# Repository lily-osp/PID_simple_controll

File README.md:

# BLDC Motor PID Controller (ESP32-C3)

Fixed-target PID controller for BLDC motors on the ESP32-C3, run bare-metal
for compute (no WiFi, no BLE). Holds 1440 RPM via a 200Hz FreeRTOS loop.

> History: this project previously shipped Arduino Uno and ATtiny85 variants.
> They were removed on 2026-10-31 (commit `396ade7`) and remain in git history.

## Overview

Single-platform implementation targeting the ESP32-C3 SuperMini. The C3 is
used for its 160MHz RISC-V core and hardware FPU; no wireless stack is used.
Two firmware builds share one set of drivers: a bench build for bring-up and
a production build for the enclosure.

| Build | Status | Use Case | Key Features |
|-------|--------|----------|--------------|
| **`esp32-c3/control/`** | Bench | Bring-up, service, Hall-line trials | Serial console, telemetry, trial scoring |
| **`esp32-c3/embedded/`** | Production | Enclosure deployment | Silent, autonomous, arming + stall failsafe |

## Key Features

- **200Hz Control Loop**: High-frequency PID updates via dedicated FreeRTOS task
- **Hardware-Accelerated PWM**: ESP32 LEDC peripheral generating smooth 5kHz motor control signals
- **Interrupt-Driven RPM**: High-precision pulse counting using IRAM-resident ISR
- **Sliding Window Filter**: 12-sample window + IIR smoothing for stable control input
- **ESC Arming + Soft-Start**: 2s zero-throttle arm, then 1.5s power ramp
- **FPU Utilization**: Full floating-point PID calculations for maximum precision
- **Safety Features**: Stall failsafe, emergency stop, input validation

## Quick Start

### 1. Hardware Requirements

- ESP32-C3 SuperMini (or compatible) + USB-C cable
- 3-Phase BLDC Motor with Hall Effect sensors
- PWM-compatible ESC / motor driver (e.g., JYQD V7.3E)
- Power supply appropriate for motor voltage requirements
- Voltage divider (2.2kΩ/3.3kΩ) if using 5V Hall sensors

### 2. Installation Steps

```bash
git clone https://github.com/your-repo/PID_simple_controll.git
cd PID_simple_controll
```

**Configure for your motor**:
1. Edit `esp32-c3/control/config.h` (pins, motor, PPR)
2. Edit `esp32-c3/control/config_common.h` (PID gains)
3. Configure pin assignments if using custom wiring

**Upload firmware**:
- Use Arduino IDE with ESP32 board support, or `arduino-cli`:

```bash
arduino-cli compile -b esp32:esp32:nologo_esp32c3_super_mini esp32-c3/embedded
arduino-cli upload  -p /dev/ttyACM0 -b esp32:esp32:nologo_esp32c3_super_mini esp32-c3/embedded
```

Which build to flash: see [esp32-c3/BUILDS.md](esp32-c3/BUILDS.md).

## Platform Details

### ESP32-C3 (`esp32-c3/`)

**Processor**: RISC-V @ 160MHz with hardware FPU

**Firmware Builds**:

**Bench (`control/`)**: Serial console for bring-up and service.
- Command parser, telemetry, diagnostics console
- Trial log auto-scores each power cycle to rank Hall permutations
- Full visibility into PID state and RPM estimation

**Production (`embedded/`)**: Silent, autonomous build for the enclosure.
- Control loop, ESC arming, soft-start, stall failsafe
- Shares the exact RPM estimator, PID, and LEDC drivers with the bench build

**Features**:
- Hardware FPU for fast floating-point calculations
- FreeRTOS ensures deterministic timing
- 3.3V logic level (requires voltage divider for 5V sensors)
- Comprehensive debugging via Serial Monitor (bench build)

Full architecture: [esp32-c3/README.md](esp32-c3/README.md).

### Custom Driver PCB (`PCB/V1/`)

Full-integration **64 × 98 mm, 4-layer** board combining the firmware above with its own
driver hardware — no external ESC needed:

- **JYQD-V7.3E3 architecture**: JY01 controller + JY213L gate driver + JY2605M
  half-bridges (same silicon as the reference driver board)
- **ESP32-C3 Super Mini** onboard as the controller (FG/PWM/VR/EL/trim pot)
- **Hall signal conditioner**: RC filter → LM324 (×11) → 74HC14 Schmitt trigger
- **Power tree**: V_IN → 7812 → +12V → 7805 → +5V

Design files, port pinouts, and build scripts: [PCB/V1/README.md](PCB/V1/README.md).
Bring-up procedure: [PCB/V1/TESTPLAN.md](PCB/V1/TESTPLAN.md).

## Documentation

### Comprehensive Guides

- **[Hardware Assembly Guide](docs/howto.md)**: Wiring guide, pin assignments, and connection diagrams
- **[Bench Wiring — stock JYQD + ESP32](docs/bench_wiring.md)**: Run the firmware on a stock JYQD-V7.3E3 and a bare Super Mini, before the custom PCB
- **[Troubleshooting Guide](docs/mitigation.md)**: Comprehensive diagnosis and solutions for common issues
- **[ESP32-C3 README](esp32-c3/README.md)**: Architecture, firmware, and hardware setup
- **[Builds](esp32-c3/BUILDS.md)**: Production vs bench firmware, and how they share code
- **[Diagnostics Guide](esp32-c3/DIAGNOSTICS.md)**: Serial console commands and fault isolation
- **[Driver PCB](PCB/V1/README.md)**: 64 × 98 mm 4-layer ESP32-C3 + JYQD-architecture driver board
- **[PCB Test Plan](PCB/V1/TESTPLAN.md)**: Staged bring-up procedure and failure diagnosis

## Configuration

### Motor Configuration

Settings live in `esp32-c3/*/config.h`:

```cpp
#define PULSES_PER_REV  4     // Set based on motor pole count
#define DEFAULT_TARGET_RPM 1440.0  // Target speed in RPM
```

**Calculating PULSES_PER_REV**: For a motor with N poles using single Hall sensor: `PULSES_PER_REV = N / 2`

Example: 8-pole motor = 4 pulses per revolution

### PID Tuning

PID constants are defined in `esp32-c3/control/config_common.h`:

```cpp
#define DEFAULT_KP  0.150  // Proportional gain
#define DEFAULT_KI  0.080  // Integral gain
#define DEFAULT_KD  0.015  // Derivative gain
```

**Tuning Process**:
1. Begin with Kp only (set Ki and Kd to 0)
2. Increase Kp until oscillation occurs, then reduce by 30%
3. Add Ki gradually to eliminate steady-state error
4. Add small Kd if overshoot occurs
5. Watch the bench console telemetry to verify stability

## Safety Considerations

1. **Electrical Isolation**: Keep logic power separate from motor power (common ground only)
2. **Voltage Protection**: Use voltage dividers when interfacing 5V sensors with 3.3V logic
3. **Mechanical Safety**: Secure motor firmly and remove propellers during initial testing
4. **Emergency Stop**: Keep power disconnect easily accessible during testing
5. **Current Rating**: Ensure power supply can handle motor startup current (typically 2-3x running current)
6. **Thermal Management**: Monitor ESC and motor temperatures during extended operation

## Troubleshooting Quick Reference

| Issue | Likely Cause | Solution |
|-------|--------------|----------|
| Motor doesn't start | Insufficient PWM threshold | Increase `PWM_MIN_THRESHOLD` to 60-80 |
| RPM reading 2x actual | Wrong `PULSES_PER_REV` | Divide current value by 2 |
| Unstable speed | Poor PID tuning or noise | Reduce Kp by 30%, add filtering |
| Random RPM spikes | Electrical noise | Add 0.1µF capacitor to Hall input |
| ESP32-C3 damaged | 5V applied to GPIO | Use voltage divider for all 5V signals |

See [Troubleshooting Guide](docs/mitigation.md) for comprehensive solutions.

## Contributing

Contributions are welcome. Areas of interest:
- Advanced PID algorithms (adaptive, fuzzy logic)
- Enhanced filtering techniques
- PCB designs for production deployment
- Test cases and validation procedures

Please read [CONTRIBUTING.md](CONTRIBUTING.md) for guidelines.

## License

MIT License - See [LICENSE](LICENSE) file for details.

This project is provided as-is for educational and commercial use. No warranty is provided for fitness for any particular purpose.

## Support

- **Issues**: Report bugs and request features via GitHub Issues
- **Discussions**: Ask questions and share experiences in GitHub Discussions
- **Documentation**: Comprehensive guides available in `docs/` directory

## Acknowledgments

Built with focus on reliability, performance, and practical deployment. Tested in real-world applications across multiple motor types and configurations.

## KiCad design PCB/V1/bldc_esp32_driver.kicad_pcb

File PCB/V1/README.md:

# BLDC Motor Driver — JYQD-V7.3E3 Architecture + ESP32-C3 Super Mini + Hall Amp

Custom **64 × 98 mm, 4-layer** PCB (full-integration) based on the **JYQD-V7.3E3** brushless driver
architecture, with an **ESP32-C3 Super Mini** controller and a Hall sensor signal
conditioner (RC filter → LM324 gain ×11 → 74HC14 Schmitt trigger).

> `JYQD-V7.3E3-English.pdf` is a product datasheet (specs + wiring), not a schematic.
> The circuit follows the JY family — **JY01** (SOP-16 controller) and **JY2605M**
> (PowerPAK SO-8 dual N-MOS, 60 V / 50 A / 14 mΩ) — the same silicon as the reference
> board. The gate driver is a **Fortior FD6288T** (TSSOP-20), which is pin-for-pin
> identical to the JY213L of the reference board but is stocked by LCSC (C97683).
> Datasheets for all three are in `docs/controller_specification/`.

## External interface (fully integrated — 3 connectors only)

Everything else is handled on-board by the ESP32 (speed/direction/enable are driven
internally to the JY01). No control port, no GPIO breakouts.

| Connector | Pins | Function | Pitch |
|---|---|---|---|
| **J5** power | `P+  P−` | +12 V (V_IN) and ground | 5.00 mm (MaiXu MX126) |
| **J6** motor | `MA  MB  MC` | phase A / B / C to BLDC | 5.00 mm (MaiXu MX126) |
| **J3** Hall | `GND  Hc  Hb  Ha  5V` | Hall sensors (powered from 5 V) | 2.54 mm |

## Architecture

```
 V_IN ── 7812 ── +12V ── 7805 ── +5V
   │                │          │
 JY01 ──gate R── FD6288T ─gate R── JY2605M ×3 ── phases A/B/C (J6)
   │                │
 Hall amp (5V): RC → LM324(×11) → 74HC14 → JY01 Hall inputs
 ESP32-C3: FG (scaled) / PWM → VR / EL / trim pot
```

- **Power tree**: `V_IN` (J5 P+) → U8 L7812 → `+12V` (gate-driver VCC) → U7 L7805 →
  `+5V` (logic). Hall amp runs on **+5V**, so 74HC14 outputs drive JY01 directly.
- **Current sense**: the bridge return (`GND`) passes through the R1 shunt (5 mΩ, 2512)
  to `PNEG` = J5 P−. **U1's `Vss` is tied to `PNEG`, not to the ground pour**, so the
  `Is` pin (fed from the `GND` side of the shunt through R36 + C21) sees a *positive*
  I·R. Referencing `Vss` to the pour instead — as V1 did — makes `Is` read negative and
  the JY01's constant-current and overload trips never fire. The offset this puts on
  U1's other pins is ≤ I·R ≈ 75 mV at 15 A, far inside its logic margins.
  Trip points, per the JY01 datasheet: constant-current at `Is` = 0.1 V (20 A across
  5 mΩ), shutdown at 0.2 V. Lower R1 to size them for a smaller motor.

## Design notes

- **78xx regulators**: with 12–36 V input keep `V_IN ≤ 28 V` for dropout/power margin
  (12 V nominal recommended).
- **PWM → VR**: GPIO1 drives the JY01 `VR` node through **R7 (100 Ω)**, directly. The
  JYQD datasheet accepts PWM 1–20 kHz on `VR` and averages it internally, so no level
  shifter is needed. Max drive is 3.3 V of the 0.1–5 V range ≈ 66 % speed.
- **GPIO4 → EL level shift**: EL is pulled up to **+5V** (R33 10 kΩ); GPIO4 drives it
  open-drain through R34 (1 kΩ). Configure GPIO4 as open-drain in firmware. Per the
  JYQD datasheet, EL high/floating **allows** operation and GND forbids it, so the
  motor is enabled by default at power-up.
- **FG scaling**: JY01 FG (5 V) → R4 2.2 k / R5 3.3 k divider → GPIO0 (RPM in, 3.3 V).
- **ESP32 pin usage**: GPIO0=RPM (FG), GPIO1=PWM→VR, GPIO2=**unconnected** (boot
  strapping pin, internal pull-up holds it high), GPIO3=trim ADC (ADC1_CH3),
  GPIO4=EL (open-drain), GPIO5=ERR LED. GPIO6–10/20/21 are spare/unconnected.
- **ERR LED** driven from GPIO5 via R32 (560 Ω); **PWR LED** from +5V via R20 (560 Ω).

## 2026-11 rework — sourcing fix + three real bugs

Driven by `tools/v2_power_stage_rework.py` (board) and `tools/gen_sch_full.py`
(schematic); both are re-runnable and idempotent. After it: **DRC 0 errors / 0
warnings / 0 unconnected**, and every pad's net matches the schematic netlist.

| # | What was wrong | What changed |
|---|---|---|
| 1 | `U3` (JY213L) is not in the LCSC catalogue | **U3 is now a Fortior FD6288T (C97683)** — same TSSOP-20 land, same pin order (1-3 HIN, 4-6 LIN, 7 VCC, 8 COM, 9-11 LO3..LO1, 12-14 VS3/HO3/VB3, 15-17 phase 2, 18-20 phase 1). 250 V instead of 90 V, 1.5/1.8 A outputs, 200 ns dead time. It has **no internal bootstrap diodes** (the JY213L does), which is why D1–D3 stay. No copper moved. |
| 2 | `Q2–Q4` used an invented DFN-8 footprint: eight 1.6 × 0.65 mm pads on opposite edges, no thermal pads — it does not match the real JY2605M and could not carry the current | **New land `footprints/JY2605M_PowerPAK_SO8_Dual.kicad_mod`**, derived from KiCad's vetted `PowerPAK_SO-8_Dual` and renumbered to the datasheet pinout **1 = S1, 2 = G1, 3 = S2, 4 = G2, 5,6 = D2, 7,8 = D1**. The symbol was rewritten to match (the old one invented `G_H/D_H/S_H/…`). |
| 3 | `U1` pins 9–12 were wired 9 = BB, 10 = BT, 11 = CB, 12 = CT | The JY01 datasheet says **9 = BT, 10 = BB, 11 = CT, 12 = CB**. On the B and C legs the chip's top-arm output drove the bottom FET and vice versa, so the motor could not commutate (no shoot-through — the JY01 never asserts both arms of one leg — but it would cog or stall). Fixed. |
| 4 | `Is` could never trip | U1's `Vss` sat on the ground pour, i.e. the **high** side of the R1 shunt, so `Is` saw a negative voltage and the constant-current and overload protections were dead. `Vss` and the C21 filter return now sit on `PNEG` (connector side); R36's cold end moved to the pour. See *Current sense* above. |

**How the half-bridge is formed.** The JY2605M is two independent FETs, not an
internally-connected half-bridge, so the board makes the bridge: D1 (left pad) = `V_IN`,
S1 (bottom-left lead) = phase, D2 (right pad) = phase, S2 = `GND`, G1/G2 = gates. Each
part is rotated 90°, drains up, leads down. The phase node therefore has to get from the
bottom-left lead to the right-hand pad: it drops to a via pair under the package, crosses
on **In1.Cu** as a 2 mm wrap, and comes back up east of the part. In1.Cu carried no
routing before, so the three wraps are the only cuts in that plane.

**Gate fan-out.** The six gate stubs drop into a via row 1.6 mm below each package and run
west-to-east on **B.Cu** in six lanes (79.6 → 82.6 mm, 0.6 mm apart), each lane joining the
existing In2.Cu run from its 15 Ω resistor at a hand-off via (x = 132.3 → 136.4 mm). Lane
depth increases as the target moves west, so no lane crosses another.

**Where the JY01 pin-order fix was made.** The chain `U1 pin → 100 Ω → FD6288T input` is
correct end to end, so the crossing is undone once, at the driver's inputs, where there is
room: the four approaches to U3 pins 2/3/5/6 are re-routed (two hops on In1.Cu, one on
B.Cu, one extended on In2.Cu). The two 100 Ω pairs are identical parts, so `R10`/`R11` and
`R12`/`R13` swap reference designators to follow the function they now serve.

**3D model.** The new footprint ships a hand-built VRML body
(`Custom.3dshapes/JY2605M_PowerPAK_SO8_Dual.wrl`) so Q2–Q4 appear as real packages in
`render/routed_top.png` instead of bare pads — the old DFN footprint had no model at all.
Representative geometry for visualisation, not mechanical clearance work.

**Test points.** TP19/TP21/TP22/TP27 (the four western gate probes) moved onto the new gate
vias and shrank to 1.0 mm; their silkscreen numbers moved with them. TP20 and TP23 are
unchanged. New coordinates are in [`TESTPLAN.md`](TESTPLAN.md).

**Still hand-fitted:** U1 (JY01) and Q2–Q4 (JY2605M) — both Shanghai Juyi parts, sold on
that company's Taobao store (shop `301588897`) and through juyitech.com; datasheets are in
`docs/controller_specification/`. If a fully LCSC-sourced power stage is ever wanted, the
drop-ins are six singles — TM80N06NF (C7422888, DFN5x6, 60 V / 80 A / 5.2 mΩ) or
NCE6050KA (C96013, TO-252) — which needs a new power-stage layout, not just a footprint.

## Pre-order audit

Checks performed on the exact fabrication data (`fab/`), all passing:

| Check | Result |
|---|---|
| DRC (`--severity-all`) | 0 violations, 0 unconnected items |
| Schematic parity | 0 genuine (266 cosmetic: root-sheet `/` prefix, footprint lib prefix) |
| Outline closure | closed Edge.Cuts loop, 0 open endpoints, 64.1 × 98.1 mm |
| Pads outside outline | 0 |
| Orphan nets (1 pad) | none |
| Fab files | 11 gerbers (4 copper) + 1 drill (Excellon, metric, decimal) + job file |
| Solder mask | 238 front / 33 rear openings (205 SMD + 29 THT + 4 NPTH); 0.05 mm expansion, 0.10 mm min web |
| Paste | 205 front apertures (1:1 with the SMD pads), none on the rear |

### Electrical fixes applied at audit

- **Bootstrap caps C13–C15 were 10 µF/25 V.** The `VB_x` rail floats on the phase and
  peaks at `V_IN + (V_+12V − V_f)` ≈ **V_IN + 11.3 V**. At the intended 12 V input that
  is 23.3 V (93 % of the rating); at 24 V input it is 35.3 V and the part fails short,
  taking the JY213L with it. Changed to **1 µF/50 V**, which is also the correct
  bootstrap value for this gate charge (droop ≈ Q_g/C ≈ 50 mV/cycle). Footprint
  unchanged (0805).
- **Unrated 0805 caps on rails** were given explicit ratings: `C12 → 10 µF/25 V` (it sits
  on +12 V), `C11/C19/C20 → 100 nF/50 V`.

### Layout changes applied at audit

1. **Trim pot moved off the strapping pin.** `RV1`'s wiper was on `GPIO2`, one of the
   three ESP32-C3 strapping pins (GPIO2/8/9), which must be high or floating at boot. The
   pot pulls it to 0 V at the low end of travel, so a power cycle with the pot turned
   down could enter joint-download boot instead of running firmware. The net now goes to
   `GPIO3` (`ADC1_CH3`, not a strapping pin); only the final 1.31 mm stub was rerouted,
   the 20 mm trunk is untouched. `GPIO2` is left floating, which is exactly the state its
   internal boot pull-up wants.
2. **Firmware followed the pin move.** `POT_SENSITIVITY_PIN` is now 3 and the
   `POT_ENABLE_PIN` gate is gone — the trim is always active and the pot midpoint is
   1.0×. Previously the firmware expected the enable on `GPIO3` while the board left it
   unconnected, so the pot did nothing at all. Both sketches compile (`pio run`,
   espressif32 7.0.1): control 17.9 % flash / 4.3 % RAM, embedded likewise.
3. **Four M3 mounting holes added** at the corner-arc centres (5 mm from each edge),
   NPTH 3.2 mm, marked board-only so they do not appear as schematic-parity extras, with
   a 1.2 mm copper-free ring so a screw head cannot short the GND pour.
4. **`C4` shifted 2.4 mm left** because its 10 mm can sat 0.4 mm from the bottom-right
   hole — an M3 head would have fouled it. Its three track endpoints were snapped to the
   new pad positions; nothing else moved.

### Remaining note

- **`EL` (GPIO4) and the ERR LED (GPIO5) are wired but unused by firmware.** `EL` is
  pulled to +5 V through R33 and driven open-drain through R34, so the JY01 enable state
  at power-up depends on the EL polarity of the JY01 itself — confirm before relying on
  the motor being disabled at boot. Wiring either up is a firmware change only.

## Status

**Folder layout:** `PCB/V1/` is this board. When a smaller revision is attempted it goes
in `PCB/V2/` alongside it, so both stay buildable and comparable.

**The previous board is preserved at git tag `v1`** (commit 837cf5a): 70 × 120 mm,
2 layers. This folder is the current 64 × 98 mm 4-layer board.

| | old (tag `v1`) | this board |
|---|---|---|
| Size | 70 × 120 mm (8400 mm²) | **64 × 98 mm (6272 mm², −25 %)** |
| Layers | 2 | **4** (In1 = solid GND plane) |
| Signal layers | 2 | 3 (F.Cu, In2.Cu, B.Cu) |
| Phase copper (avg) | 0.33–0.39 mm | **0.67–0.74 mm** |
| Traces / vias | 1277 / 142 | 862 / 121 |
| DRC | 0 / 0 | 0 / 0 |

- **Schematic**: complete & verified — netlist matches the design table **223/234 pins**
  (floating pins are the 3 unused 74HC14 gate outputs + 8 spare ESP32 GPIOs).
- **Board**: **fully routed, DRC-clean, fab package generated** — 64.1 mm × 98.1 mm
  (5 mm rounded corners), 97 footprints (67 components + 4 M3 holes + 26 test points).
  - 862 traces, 121 vias, 4 zones (solid GND plane on In1 + GND pours on
    F.Cu / B.Cu / In2.Cu)
  - **DRC: 0 violations, 0 unconnected items** (`kicad-cli pcb drc --severity-all`)
  - **Schematic parity: 0 genuine mismatches** — the 266 reported items are cosmetic only
    (schematic nets carry the root-sheet `/` prefix; footprints are reported without their
    library prefix). Verified programmatically: 0 net-name differences, 0 footprint
    differences after normalisation, 0 extra footprints.
  - **Outline**: closed Edge.Cuts loop, 0 open endpoints; **0 pads outside** the outline.
  - **Drills**: 0.3 mm ×110 and 0.4 mm ×15 (vias), 0.8/1.0/1.1/1.2/1.3 mm ×29
    (component holes), 3.2 mm ×4 (M3 mounting, NPTH).
  - Renders: `render/routed_top.png`, `render/routed_bottom.png`
  - **Bottom silkscreen**: OSP cloud logo (16 mm, vectorised from
    `OSP_1600.png` with potrace into 14 filled polygons) and the credit
    `designed by : github.com/1999azzar`, both on `B.SilkS`.

### Copper sizing (measured, not assumed)

The 4-layer stack gives the phases a dedicated corridor, so they are no longer starved by the 2-layer
clearance wall. Length-weighted averages:

| Net | 2-layer avg | V1 avg | **after the rework** | min | max |
|---|---|---|---|---|---|
| PH_A | 0.33 mm | 0.75 mm | **0.86 mm** | 0.25 mm | 2.00 mm |
| PH_B | 0.35 mm | 0.74 mm | **0.88 mm** | 0.25 mm | 2.00 mm |
| PH_C | 0.39 mm | 0.77 mm | **0.94 mm** | 0.25 mm | 2.00 mm |
| V_IN | 0.80 mm | 0.79 mm | **1.19 mm** | 0.80 mm | 1.50 mm |
| PNEG | 0.80 mm | 0.80 mm | 0.66 mm | 0.40 mm | 0.80 mm |
| +12V / +5V | 0.57 mm | 0.40 mm | 0.40 mm | 0.40 mm | 0.40 mm |

> **Current capability.** Inside the power stage the phase node is a 2.00 mm In1.Cu wrap
> and the V_IN rail is 1.50 mm on 2 oz outer copper; the narrowest part of a phase path is
> the 0.80 mm stub out of the high-side source lead. By IPC-2221 at a 20 °C rise that stub
> sets the limit at **≈ 4.5 A continuous per phase**, with the rest of the path good for
> 8–11 A, and the low-side return leaves through the pour and a via into all four planes.
> That covers the 42BLF motor family's 1.9–5.7 A rated current; it is **not** the 15 A the
> JYQD-V7.3E3 reference board claims, and the board should not be run there.
> `PNEG` now carries only the sense reference and the logic return, so its 0.40 mm
> branches are fine. The `+12V`/`+5V` rails stay at 0.40 mm (~1.5 A on 2 oz) against a
> load of a few hundred mA.

## Component placement (64 × 98 mm)

| Zone | Components |
|---|---|
| Top edge | J5 (power in), J6 (motor out), M3 holes in the corners |
| Bottom edge | J3 (Hall port) |
| Left column | C1/C2/C5 bulk → U8 (7812) → C3 → U7 (7805) → C4, i.e. the whole power chain |
| Under J6 | Q2/Q3/Q4 (JY2605M) with R1 shunt |
| Right of the FETs | U3 (FD6288T), bootstrap C13–C15 + D1–D3, gate resistors R14–R19 |
| Middle | U1 (JY01) + R8–R13, then the Hall amp (U4 LM324, U5 74HC14, R21–R31) |
| Bottom | U6 (ESP32-C3), RV1, LEDs |

`U3` sits clear of the FET row on purpose: its 0.65 mm-pitch phase-sense pins need a
fanout corridor, and placing it in line with the FETs makes them unreachable.

## Routing pipeline (reproducible)

1. `gen_sch_full.py` — regenerate schematic (netlist-verified).
2. `compact_4l.py` — the placement + 64 × 98 mm rounded outline, with a courtyard
   clash report (`--check` reports without saving).
3. `route_prep_4l.py` — export the DSN and inject width classes. **In1.Cu is set to
   `power`**, so FreeRouting will not put signal traces on it and it stays a solid plane.
4. FreeRouting **2.1.0** on Java 21:
   `java -jar freerouting.jar -de board.dsn -do board.ses -mp 40 -mt 1`
   (single-threaded; the multi-threaded optimizer creates clearance violations).
5. `import_4l.py` — import the session, (re)create the GND plane + pours, refill.
6. `fix_open_nets_4l.py NET...` — rip a few nets and re-route them with everything else
   frozen, when the router leaves a handful open.
7. `silk_4l.py` — hide passive reference designators and clear silkscreen warnings.
8. `fab_package.sh [--2oz]` — gerbers + drill + positions + `fab/ORDER.md`.

**Five things that cost hours, documented so they don't again:**

- KiCad exports a GND pour as a full-board Specctra `(plane ...)` on **every** copper
  layer. If the pours are present during export, FreeRouting sees an occupied board and
  plateaus at ~90+ unrouted. Remove the zones before export, refill afterwards.
- `board.Remove(item)` silently does nothing in this pcbnew build. Use `board.Delete(item)`
  — the failure mode is invisible (the board keeps its old tracks) and costs a full
  routing run to notice.
- FreeRouting can finish routing and then hang before writing the `.ses`. The cause is
  stale `java` processes from earlier runs; `kill -9` every `java` before starting.
- A `0.65 mm`-pitch TSSOP cannot fan out three sense pins into a via between adjacent
  pads. It needs ~3 mm of clear corridor above the pin row; that is what drove the
  power-stage placement.
- On a 4-layer board the zones can end up as several filled islands. Stitch them to the
  In1 plane with GND vias, otherwise DRC reports the pour as unconnected.
- KiCad writes the inner copper layers with their internal layer IDs (`Copper,L5,Inr`,
  `L7`) into the `.gbrjob` even though the gerbers themselves carry the correct `L2`/`L3`.
  `fab_package.sh` rewrites the job file so CAM cannot read a 4-layer stack as 8-layer.
- A 3D render with no model library looks like a bare board with random pads, which reads
  as "the placement is broken". This machine has no `kicad-packages3d` installed; the
  models are fetched with `nix build nixpkgs#kicad.libraries.packages3d` and are shipped
  as **zip files named `.stpZ`**, not zstd. Unzip the ones the board references and point
  `KICAD9_3DMODEL_DIR` at the result:
  `KICAD9_3DMODEL_DIR=<dir> kicad-cli pcb render ...`
  This project's models are installed at `~/.local/share/kicad/3dmodels` and the path is
  registered in `~/.config/kicad/9.0/kicad_common.json`, so a plain render works.
- **U6 (ESP32-C3 SuperMini) has no official 3D model.** It is a third-party board, so it
  is not in the Espressif library (which covers ESP32-C3-MINI-1/WROOM-02 only), and the
  GrabCAD/Printables/SnapEDA models need an account. A dimensionally correct
  representative body (22.5 x 18 x 1.6 mm + USB-C + antenna area) is used instead,
  from `Custom.3dshapes/ESP32-C3-SuperMini.wrl`. It is for visualisation, not mechanical
  clearance work.
- **Q2-Q4 (JY2605M) have no vendor 3D model either** - Shanghai Juyi publishes an outline
  drawing only, and the part is not in KiCad's library. A hand-built representative body
  (6.15 x 5.15 x 1.05 mm, both lead rows, the pin-1 chamfer and the two exposed drain
  pads) is used, from `Custom.3dshapes/JY2605M_PowerPAK_SO8_Dual.wrl`, generated from the
  same geometry as the land pattern. Visualisation only, like U6. Without it the three
  FETs render as bare pads and the power stage reads as unpopulated.
  The source is kept in the repo at `3dmodels/JY2605M_PowerPAK_SO8_Dual.wrl` (it exists
  nowhere else); copy it to `~/.local/share/kicad/3dmodels/Custom.3dshapes/` on a new
  machine, alongside `ESP32-C3-SuperMini.wrl`, before rendering.
- The mask gerbers are emitted as **G36/G37 region fills**, not aperture flashes. Counting
  `%ADD`/`D03` in them reports zero and looks catastrophic; count `G36` instead.

## Ordering

```bash
./tools/fab_package.sh --2oz     # 2 oz outer copper; drop the flag for 1 oz
```

Output in `fab/`:

| File | Contents |
|---|---|
| `bldc_esp32_driver_gerbers.zip` | 11 gerbers (4 copper, 2 mask, 2 silk, 2 paste, Edge.Cuts) + `.drl` |
| `positions.csv` | assembly centroids, mm, drill origin |
| `ORDER.md` | board spec sheet to hand to the fab |

Verification already passed on this exact board: 0 DRC violations, 0 unconnected items,
closed outline, 0 pads outside the outline, 0 genuine schematic-parity mismatches.

### Assembly (PCBA)

The board is set up to be ordered **assembled**, with these deliberately left
unpopulated (marked DNP in both the schematic and the board, so the BOM and CPL
exclude them automatically):

| Ref | Part | Why |
|---|---|---|
| U6 | ESP32-C3 SuperMini | third-party module, fitted by hand |
| J3 | 1x05 2.54 mm header | no headers wanted — wires go straight to the pads |
| J5 | MX126 2-pin terminal | power wires soldered directly |
| J6 | MX126 3-pin terminal | motor wires soldered directly |

**Four parts cannot be bought from LCSC**: **U1 (JY01)** and **Q2–Q4 (JY2605M)**.
Shanghai Juyi — the company behind the JYQD boards — sells both from its own
Taobao store (shop `301588897`, JY01(8559) or JY01(6281) ≈ CNY 5.4, JY2605M
≈ CNY 2.5) and through juyitech.com / Alibaba. Hand-solder them, or send them to
JLCPCB as consigned parts. **U3 is now an FD6288T (C97683)**, so the gate driver
is no longer in that list.

**Test points.** Twenty-six probe pads are on the board, each with its number
printed on the silkscreen next to it. TP1–TP27 are top-side pads; TP28 is a
bottom-side pad over an existing `HALL_OUT_A` via. They cover the rails (`V_IN`,
`PNEG`, `+12V`, `+5V`, `+3.3V`, `GND`), the control path (`VR`, `ZF`,
`PWM_OUT`, `RPM_IN`, `GPIO4`, `POT_ADC`), the analogue front end (`ISENSE_F`,
`HALL_OUT_A`, `HALL_OUT_B`, `HALL_OUT_C`) and the power stage (`VB_A`,
`VB_B`, `VB_C` and all six FET gates).

Only `GPIO5` remains a component-pad probe at R32 pin 1 because the nearby ESP32
escape has no legal branch site at the board's 0.20 mm clearance rule. The pads
are board-only and excluded from the BOM/CPL, so they cost nothing. Positions,
expected voltages and a staged bring-up procedure are in [`TESTPLAN.md`](TESTPLAN.md).

The through-hole parts (C1–C5, U7, U8, RV1) are in the CPL, but JLCPCB's
economical PCBA is SMD-only — use their through-hole option or solder those by
hand as well.

`fab/bom_jlcpcb.csv` (27 lines) and `fab/cpl_jlcpcb.csv` (65 placements) are in
JLCPCB's upload format.

**LCSC part numbers** come from `tools/lcsc_map.csv` (mapping + manufacturer part),
each verified against live LCSC/JLCPCB stock. Only two lines remain blank, and only
because LCSC does not carry them:

| Line | Why |
|---|---|
| U1 (JY01), Q2–Q4 (JY2605M) | Juyi house parts, not in the LCSC catalogue |

Values that changed so the parts are actually orderable:

- `C1/C2` are **470 µF/63 V** — 480 µF is not a real capacitor value.
- `C3–C5` are 220 µF/50 V, D10 × 12.5 mm, **5 mm pitch** (matches the D10/P5 land).
- `R1` is a 5 mΩ ±1 % **3 W** 2512 shunt.
- **U2 and R6 are gone.** The old VR interface was an open-drain N-MOSFET with a
  5 V pull-up, which **inverted** the speed control — idle became full speed and the
  PID ran as positive feedback. It was also built around `CSD13380F3`, a 0.73 × 0.64 mm
  TI FemtoFET that cannot sit on the SOT-23-3 land. Both parts were removed and R7 now
  feeds `VR` directly.

> **ERC note**: the schematic reports 28 ERC items, all accounted for — 11 unconnected
> pins are the intentionally-unused 74HC14 gates and spare ESP32 GPIOs; 3 are library
> version/resolution warnings; the rest are power-flag bookkeeping (`V_IN` and the JY01
> `Vss` are fed from external connectors, which ERC wants a `PWR_FLAG` for). None affect
> the manufactured board.

## Files

```
bldc_esp32_driver/
├── bldc_esp32_driver.kicad_sch    # schematic
├── bldc_esp32_driver.kicad_pcb    # board (64 x 98 mm, 4 layers, DRC-clean)
├── bldc_esp32_driver.kicad_pro
├── README.md                      # this file
├── TESTPLAN.md                    # staged bring-up procedure
├── footprints/ESP32-C3-SuperMini.kicad_mod
├── footprints/JY2605M_DFN8_5x6.kicad_mod   # DFN-8 5x6 half-bridge (no exact lib match)
├── render/routed_{top,bottom,top_zoom}.png # refreshed by fab_package.sh
├── fab/                           # gerbers, drill, ORDER.md, BOM + CPL (JLCPCB)
├── tools/gen_sch_full.py, gen_pcb.py, verify_net.py
├── tools/compact_4l.py, route_prep_4l.py, import_4l.py, fix_open_nets_4l.py
├── tools/add_testpoints.py, make_jlcpcb_assembly.py, lcsc_map.csv
├── tools/silk_4l.py, set_values.py, fix_pot_pin_and_holes.py
├── tools/final_{incremental,import_ses,widen,settle,minwidth,silk_cleanup}.py
├── tools/fab_package.sh           # gerbers + BOM/CPL + renders in one shot
├── fp-lib-table
└── fp-info-cache
```

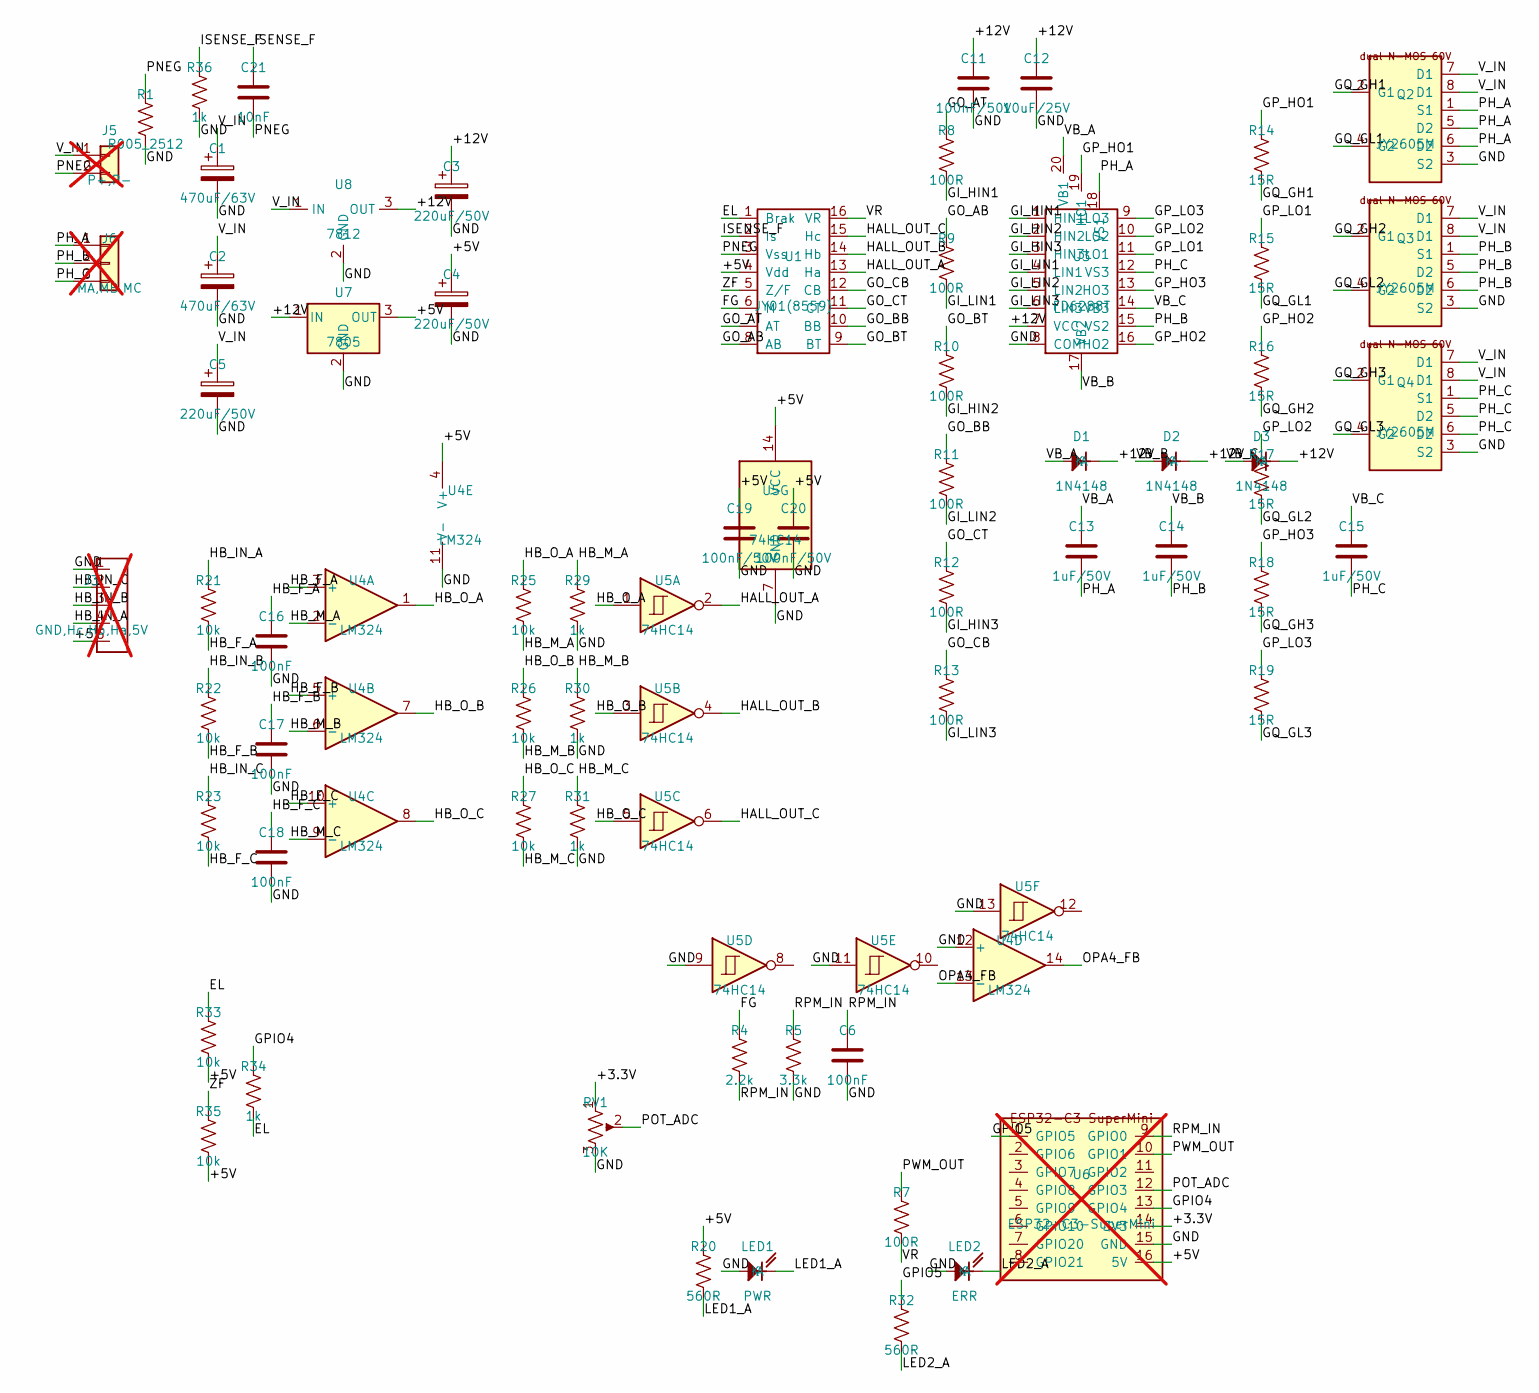
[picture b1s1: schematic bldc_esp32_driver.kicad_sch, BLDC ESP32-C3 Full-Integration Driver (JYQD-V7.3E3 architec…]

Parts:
C1, C2: 470uF/63V; CP_Radial_D13.0mm_P5.00mm
C3, C4, C5: 220uF/50V; CP_Radial_D10.0mm_P5.00mm
C6, C16, C17, C18: 100nF; C_0805_2012Metric
C11, C19, C20: 100nF/50V; C_0805_2012Metric
C12: 10uF/25V; C_0805_2012Metric
C13, C14, C15: 1uF/50V; C_0805_2012Metric
C21: 10nF; C_0805_2012Metric
D1, D2, D3: 1N4148; D_SOD-123
J3: GND,Hc,Hb,Ha,5V; PinHeader_1x05_P2.54mm_Vertical; not fitted
J5: P+,P-; TerminalBlock_MaiXu_MX126-5.0-02P_1x02_P5.00mm; not fitted
J6: MA,MB,MC; TerminalBlock_MaiXu_MX126-5.0-03P_1x03_P5.00mm; not fitted
LED1: PWR; LED_0805_2012Metric
LED2: ERR; LED_0805_2012Metric
Q2, Q3, Q4: JY2605M; JY2605M_PowerPAK_SO8_Dual
R1: R005_2512; R_2512_6332Metric
R4: 2.2k; R_0805_2012Metric
R5: 3.3k; R_0805_2012Metric
R7, R8, R9, R10, R11, R12, R13: 100R; R_0805_2012Metric
R14, R15, R16, R17, R18, R19: 15R; R_0805_2012Metric
R20, R32: 560R; R_0805_2012Metric
R21, R22, R23, R25, R26, R27, R33, R35: 10k; R_0805_2012Metric
R29, R30, R31, R34, R36: 1k; R_0805_2012Metric
RV1: 10K; Potentiometer_Bourns_3296W_Vertical
U1: JY01(8559); SOP-16_3.9x9.9mm_P1.27mm
U3: FD6288T; TSSOP-20_4.4x6.5mm_P0.65mm
U4: LM324; SOIC-14_3.9x8.7mm_P1.27mm
U5: 74HC14; SOIC-14_3.9x8.7mm_P1.27mm
U6: ESP32-C3-SuperMini; not fitted
U7: 7805; TO-220-3_Vertical
U8: 7812; TO-220-3_Vertical

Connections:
+3.3V: RV1.1, U6.14 (3V3)
+5V: C4.1, C19.1, C20.1, J3.5, R20.1, R33.2, R35.2, U1.4 (Vdd), U4.4 (V+), U5.14 (VCC), U6.16 (5V), U7.3 (OUT)
+12V: C3.1, C11.1, C12.1, D1.2 (A), D2.2 (A), D3.2 (A), U3.7 (VCC), U7.1 (IN), U8.3 (OUT)
EL: R33.1, R34.2, U1.1 (Brak)
FG: R4.1, U1.6 (M)
GI_HIN1: R8.2, U3.1 (HIN1)
GI_HIN2: R10.2, U3.2 (HIN2)
GI_HIN3: R12.2, U3.3 (HIN3)
GI_LIN1: R9.2, U3.4 (LIN1)
GI_LIN2: R11.2, U3.5 (LIN2)
GI_LIN3: R13.2, U3.6 (LIN3)
GND: C1.2, C2.2, C3.2, C4.2, C5.2, C6.2, C11.2, C12.2, C16.2, C17.2, C18.2, C19.2, C20.2, J3.1, LED1.1 (K), LED2.1 (K), Q2.3 (S2), Q3.3 (S2), Q4.3 (S2), R1.2, R5.2, R29.2, R30.2, R31.2, R36.2, RV1.3, U3.8 (COM), U4.11 (V-), U4.12 (+), U5.7 (GND), U5.9, U5.11, U5.13, U6.15 (GND), U7.2 (GND), U8.2 (GND)
GO_AB: R9.1, U1.8 (AB)
GO_AT: R8.1, U1.7 (AT)
GO_BB: R11.1, U1.10 (BB)
GO_BT: R10.1, U1.9 (BT)
GO_CB: R13.1, U1.12 (CB)
GO_CT: R12.1, U1.11 (CT)
GPIO4: R34.1, U6.13 (GPIO4)
GPIO5: R32.1, U6.1 (GPIO5)
GP_HO1: R14.1, U3.19 (HO1)
GP_HO2: R16.1, U3.16 (HO2)
GP_HO3: R18.1, U3.13 (HO3)
GP_LO1: R15.1, U3.11 (LO1)
GP_LO2: R17.1, U3.10 (LO2)
GP_LO3: R19.1, U3.9 (LO3)
GQ_GH1: Q2.2 (G1), R14.2
GQ_GH2: Q3.2 (G1), R16.2
GQ_GH3: Q4.2 (G1), R18.2
GQ_GL1: Q2.4 (G2), R15.2
GQ_GL2: Q3.4 (G2), R17.2
GQ_GL3: Q4.4 (G2), R19.2
HALL_OUT_A: U1.13 (Ha), U5.2
HALL_OUT_B: U1.14 (Hb), U5.4
HALL_OUT_C: U1.15 (Hc), U5.6
HB_F_A: C16.1, R21.2, U4.3 (+)
HB_F_B: C17.1, R22.2, U4.5 (+)
HB_F_C: C18.1, R23.2, U4.10 (+)
HB_IN_A: J3.4, R21.1
HB_IN_B: J3.3, R22.1
HB_IN_C: J3.2, R23.1
HB_M_A: R25.2, R29.1, U4.2 (-)
HB_M_B: R26.2, R30.1, U4.6 (-)
HB_M_C: R27.2, R31.1, U4.9 (-)
HB_O_A: R25.1, U4.1, U5.1
HB_O_B: R26.1, U4.7, U5.3
HB_O_C: R27.1, U4.8, U5.5
ISENSE_F: C21.1, R36.1, U1.2 (Is)
LED1_A: LED1.2 (A), R20.2
LED2_A: LED2.2 (A), R32.2
OPA4_FB: U4.13 (-), U4.14
PH_A: C13.2, J6.1, Q2.1 (S1), Q2.5 (D2), Q2.6 (D2), U3.18 (VS1)
PH_B: C14.2, J6.2, Q3.1 (S1), Q3.5 (D2), Q3.6 (D2), U3.15 (VS2)
PH_C: C15.2, J6.3, Q4.1 (S1), Q4.5 (D2), Q4.6 (D2), U3.12 (VS3)
PNEG: C21.2, J5.2, R1.1, U1.3 (Vss)
POT_ADC: RV1.2, U6.12 (GPIO3)
PWM_OUT: R7.1, U6.10 (GPIO1)
RPM_IN: C6.1, R4.2, R5.1, U6.9 (GPIO0)
VB_A: C13.1, D1.1 (K), U3.20 (VB1)
VB_B: C14.1, D2.1 (K), U3.17 (VB2)
VB_C: C15.1, D3.1 (K), U3.14 (VB3)
VR: R7.2, U1.16 (VR)
V_IN: C1.1, C2.1, C5.1, J5.1, Q2.7 (D1), Q2.8 (D1), Q3.7 (D1), Q3.8 (D1), Q4.7 (D1), Q4.8 (D1), U8.1 (IN)
ZF: R35.1, U1.5 (Z/F)

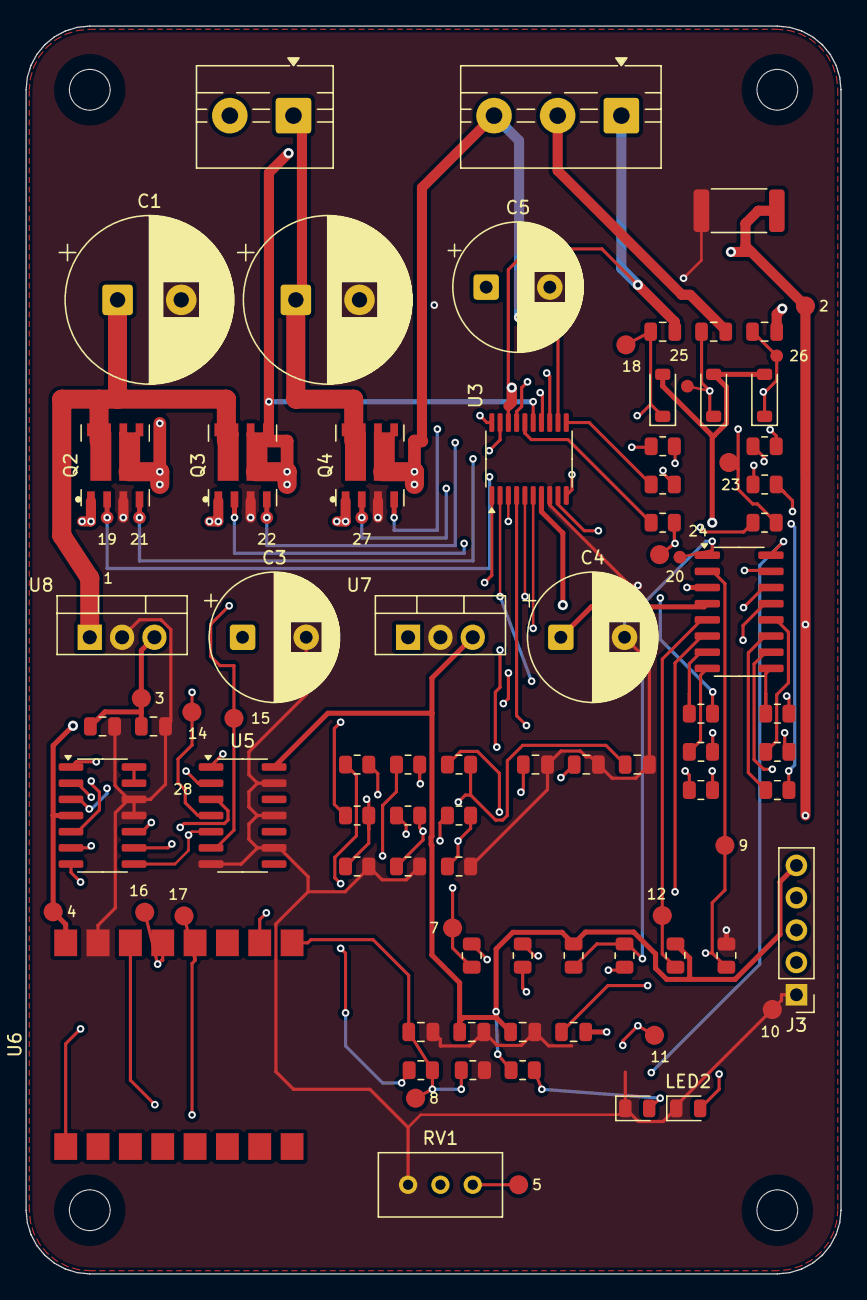
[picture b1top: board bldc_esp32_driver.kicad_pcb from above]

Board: 4 copper layers, 64.0 x 98.0 mm, 97 parts (0 on the bottom side), 64 nets.

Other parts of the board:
H1, H2, H3, H4: MountingHole_3.2mm_M3
TP1, TP2, TP3, TP4, TP5, TP7, TP8, TP9, TP10, TP11, TP12, TP14, TP15, TP16, TP17, TP18, TP19, TP20, TP21, TP22, TP23, TP24, TP25, TP26, TP27, TP28: (no value)

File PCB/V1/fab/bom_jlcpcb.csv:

Comment,Designator,Footprint,LCSC Part #
470uF/63V,"C1,C2",Capacitor_THT:CP_Radial_D13.0mm_P5.00mm,C47344187
220uF/50V,C3-C5,Capacitor_THT:CP_Radial_D10.0mm_P5.00mm,C165644
100nF,"C6,C16-C18",Capacitor_SMD:C_0805_2012Metric,C49678
100nF/50V,"C11,C19,C20",Capacitor_SMD:C_0805_2012Metric,C49678
10uF/25V,C12,Capacitor_SMD:C_0805_2012Metric,C15850
1uF/50V,C13-C15,Capacitor_SMD:C_0805_2012Metric,C28323
10nF,C21,Capacitor_SMD:C_0805_2012Metric,C1710
1N4148,D1-D3,Diode_SMD:D_SOD-123,C2099
PWR,LED1,LED_SMD:LED_0805_2012Metric,C84256
ERR,LED2,LED_SMD:LED_0805_2012Metric,C84256
JY2605,Q2-Q4,local:JY2605M_DFN8_5x6,
R005_2512,R1,Resistor_SMD:R_2512_6332Metric,C2903482
2.2k,R4,Resistor_SMD:R_0805_2012Metric,C17520
3.3k,R5,Resistor_SMD:R_0805_2012Metric,C204416
100R,R7-R13,Resistor_SMD:R_0805_2012Metric,C17408
15R,R14-R19,Resistor_SMD:R_0805_2012Metric,C20142755
560R,"R20,R32",Resistor_SMD:R_0805_2012Metric,C5576051
10k,"R21-R23,R25-R27,R33,R35",Resistor_SMD:R_0805_2012Metric,C17414
1k,"R29-R31,R34,R36",Resistor_SMD:R_0805_2012Metric,C2073872
10K,RV1,Potentiometer_THT:Potentiometer_Bourns_3296W_Vertical,C34846
JY01(8559),U1,Package_SO:SOP-16_3.9x9.9mm_P1.27mm,
JY213L,U3,Package_SO:TSSOP-20_4.4x6.5mm_P0.65mm,
LM324,U4,Package_SO:SOIC-14_3.9x8.7mm_P1.27mm,C127953
74HC14,U5,Package_SO:SOIC-14_3.9x8.7mm_P1.27mm,C130461
7805,U7,Package_TO_SOT_THT:TO-220-3_Vertical,C111887
7812,U8,Package_TO_SOT_THT:TO-220-3_Vertical,C105651

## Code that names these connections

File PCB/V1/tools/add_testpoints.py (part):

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
# reference to reuse when a pad is being re-placed after a layout change, so the
# numbers already printed in TESTPLAN.md stay valid
PREFER = {"+3.3V": "TP5", "RPM_IN": "TP8", "GPIO5": "TP13"}
MM = 1_000_000
PAD_D = 0.8 if MICRO else (1.0 if COMPACT else 1.5)
PAD_CLEARANCE = 0.15 if MICRO else (0.20 if COMPACT else 0.30)
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
# nets worth probing during bring-up
TARGETS = ["V_IN", "PNEG", "+12V", "+5V", "+3.3V", "VR", "EL", "ZF",
           "PWM_OUT", "RPM_IN", "ISENSE_F", "GPIO5",
           "HALL_OUT_A", "HALL_OUT_B", "HALL_OUT_C", "GND",
           # second pass: enable chain, analogue front end, power stage
           "GPIO4", "POT_ADC",
           "VB_A", "VB_B", "VB_C",
           "GQ_GH1", "GQ_GH2", "GQ_GH3", "GQ_GL1", "GQ_GL2", "GQ_GL3"]

# GPIO5 is intentionally left on the existing R32 probe location in compact
# mode: the nearby ESP32 pad has only 0.148 mm of clearance from its existing
# escape, so adding a branch would violate the board's 0.20 mm rule.
if COMPACT or MICRO:
    TARGETS = [net for net in TARGETS if net != "GPIO5"]

b = pcbnew.LoadBoard(BOARD)
b.BuildConnectivity()
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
